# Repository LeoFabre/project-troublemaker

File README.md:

# 🚨PROJECT TROUBLEMAKER🚨 - ABANDONED, new project coming very soon
### The original dub soundsystem-style, fully digital, open source music preamp, based on ELK Audio OS.

This project is meant to be a fully digital sound system preamp, with a lot of features and a lot of fun to use. 
This would typically be used in a dub sound system control tower, right before the DSPs and power amps.
I am making it for [my own dub sound system](https://linktr.ee/mooncrownsoundsystem), but I am sharing it with the world so that everyone can enjoy and contribute to it.

### **_[Figma design of the front plate (click to open in figma) :](https://www.figma.com/design/a7w33TZh6XjIDETXx0zezs/PROJECT-TROUBLEMAKER?node-id=2-57&t=kPiumWiky9OcTQFE-1)_**

Please note that this project is still in its early stages, and it is not yet ready for use.
Also, the aim is not to provide a classic preamp to use with a microphone, but rather a preamp to use with a line-level signal, like a CD player, a computer, a synthesizer, etc.
It will NOT provide any protection for your speakers, and also will not split the signal into multiple bands outputs. 

It is meant to be used with a DSP that can handle multiple outputs, and optionally a mixer before it, to get microphone inputs and other line-level inputs.

**At the moment, the inputs and outputs are stereo only**, but more input modes will be added in the future (see Signal Flow section).

# [Software & Hardware stack (Click to open in whimsical)](https://whimsical.com/project-troublemaker-project-diagram-5eJmr8VAKfvCzGg2v3uwR2)

Project Troublemaker is based on [ELK Audio OS](https://elk-audio.github.io/elk-docs/html/index.html), which is a Linux-based realtime audio OS that can run VST3 plugins.  
It is **_HIGHLY RECOMMENDED_** to get a grasp of ELK Audio OS before diving into this project.

I use a [Raspberry pi 4 (8GB)](https://www.raspberrypi.com/products/raspberry-pi-4-model-b/) as the main board, 

a [HifiBerry DAC+ ADC Pro](https://www.hifiberry.com/shop/boards/hifiberry-dac-adc-pro/), to get audio I/O,

a [Teensy 4.1](https://www.pjrc.com/store/teensy41.html) as the control board, which acts as a MIDI controller and communicates with the Raspberry Pi via USB.

To build the control panel I use [CD74HC4067 multiplexers](https://www.amazon.fr/ICQUANZX-CD74HC4067-Analogique-Multiplexeur-Num%C3%A9rique/dp/B07VF14YNG), and a lot of [arcade buttons](https://www.smallcab.net/sanwa-obsc-24mm-translucent-pushbutton-purple-p-2462.html), [potentiometers](https://www.amazon.fr/dp/B07B64MWRF?ref=ppx_yo2ov_dt_b_fed_asin_title), [RGB LED sticks](https://fr.aliexpress.com/item/1005006344542138.html), and [switches](https://amazon.fr/dp/B09W4HBXJ7).

The project is meant to be a fully open source project, with all the source code and hardware design files available for free.

**_Because I strongly believe that music is meant to be shared, and music gear should be open source._**

Please feel free to contribute by opening a PR or an issue. 

**_Keep in mind that I am still learning, and that I am doing this project in my free time_**, so I may take some time to get back to you and updates may be slow.

# Featured Plugins (Work in Progress)
- **_[SampleTower](https://github.com/LeoFabre/SampleTower)_** : My JUCE-based VST3 sample player. features 11 fully-loaded-in-RAM sample slots, real-time playback speed control, sample loading from the file system (via config file), sample triggering with a MIDI note, one-shot and loop modes for each sample (via config file), kill button that stops all currently playing samples.
- 2 parametric EQs with bypass switches.
- **_[Moses](https://github.com/LeoFabre/Moses)_** : My fork of [IEM's multiband compressor](https://git.iem.at/audioplugins/IEMPluginSuite/-/tree/master/MultiBandCompressor?ref_type=heads). It is a 4-band SIMD optimized multiband compressor/crossover plugin, featuring cascaded Butterworth, linkwitz-riley filters and Allpass filters, solo&kill switches and master controls.
- **_[Strange Returns](https://github.com/LeoFabre/StrangeReturns-CMake)_** : My fork of JackWithOneEye's [Strange Returns](https://github.com/JackWithOneEye/StrangeReturns) delay plugin. 
- **_[Graindr](https://github.com/LeoFabre/Graindr)_** : My fork of JackWithOneEye's [Graindr](https://github.com/JackWithOneEye/Graindr), dual granular delay plugin.
- **_Parametric Reverb FX_** : A parametric reverb that I have yet to design. The reverb pots on the frontplate are inspired by ableton's reverb plugin, and are subject to change.
- **_Sub Roar FX_** : A classic dub sub bass roar effect based on saturation, and filtering, and reverb. It is only composed of BrickWorks plugins that ELK Audio OS provides, I may or may not make a JUCE version of it in the future.

# [Signal Flow (click to open in whimsical)](https://whimsical.com/project-troublemaker-signal-flow-PksJ2XxrEqBQ8Brrcc3UFW)

## Input modes
- **_Stereo mode_**: The default mode, where the HifiBerry is used as a stereo input and output.
- **_Aux send mode_** (to be implemented): The 2 stereo channels of the HifiBerry are split in 2 mono input channels and 2 mono output channels.   
The first mono input channel is used as the main input, the first mono output is used as the main output, the second mono input channel is used as the aux send, and the second mono input channel is used as the aux return.   
This is useful to send the signal to an external effect processor and get it back in the preamp, like a reverb or a delay, and then use the preamp's processing on it.

As of now, the modes are not implemented, and the preamp only works in stereo mode.  
In the future, I will add a switch to select the input mode at boot time (Sushi would then get its processor graph built by the glue app via gRPC instead of the config file).

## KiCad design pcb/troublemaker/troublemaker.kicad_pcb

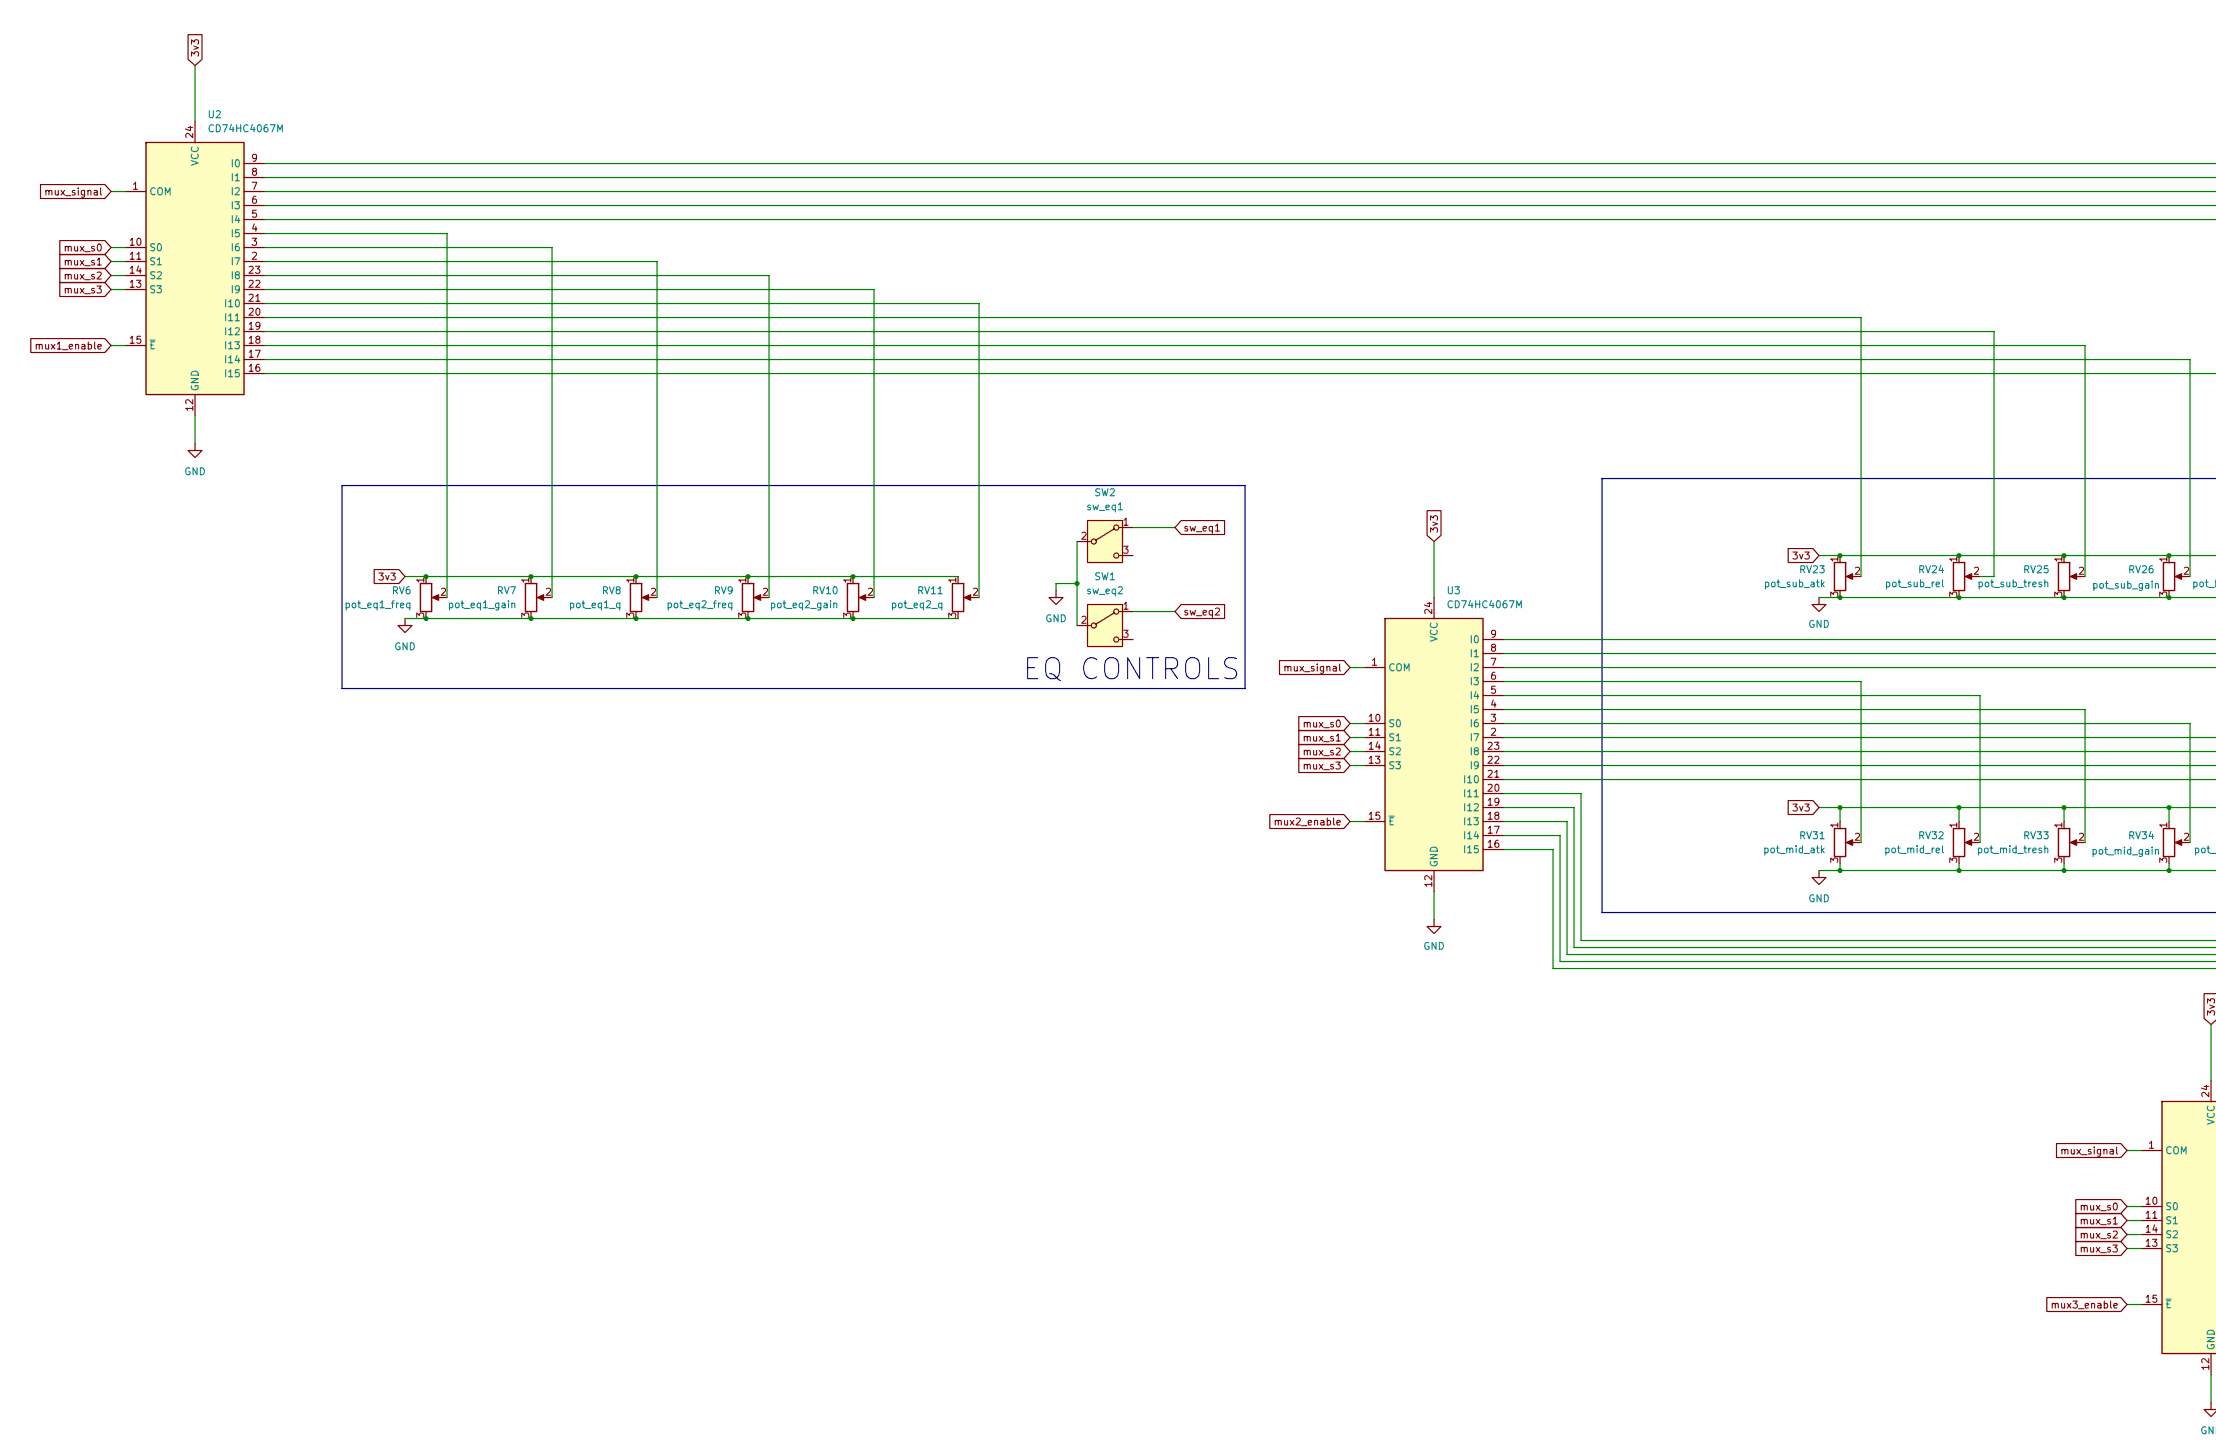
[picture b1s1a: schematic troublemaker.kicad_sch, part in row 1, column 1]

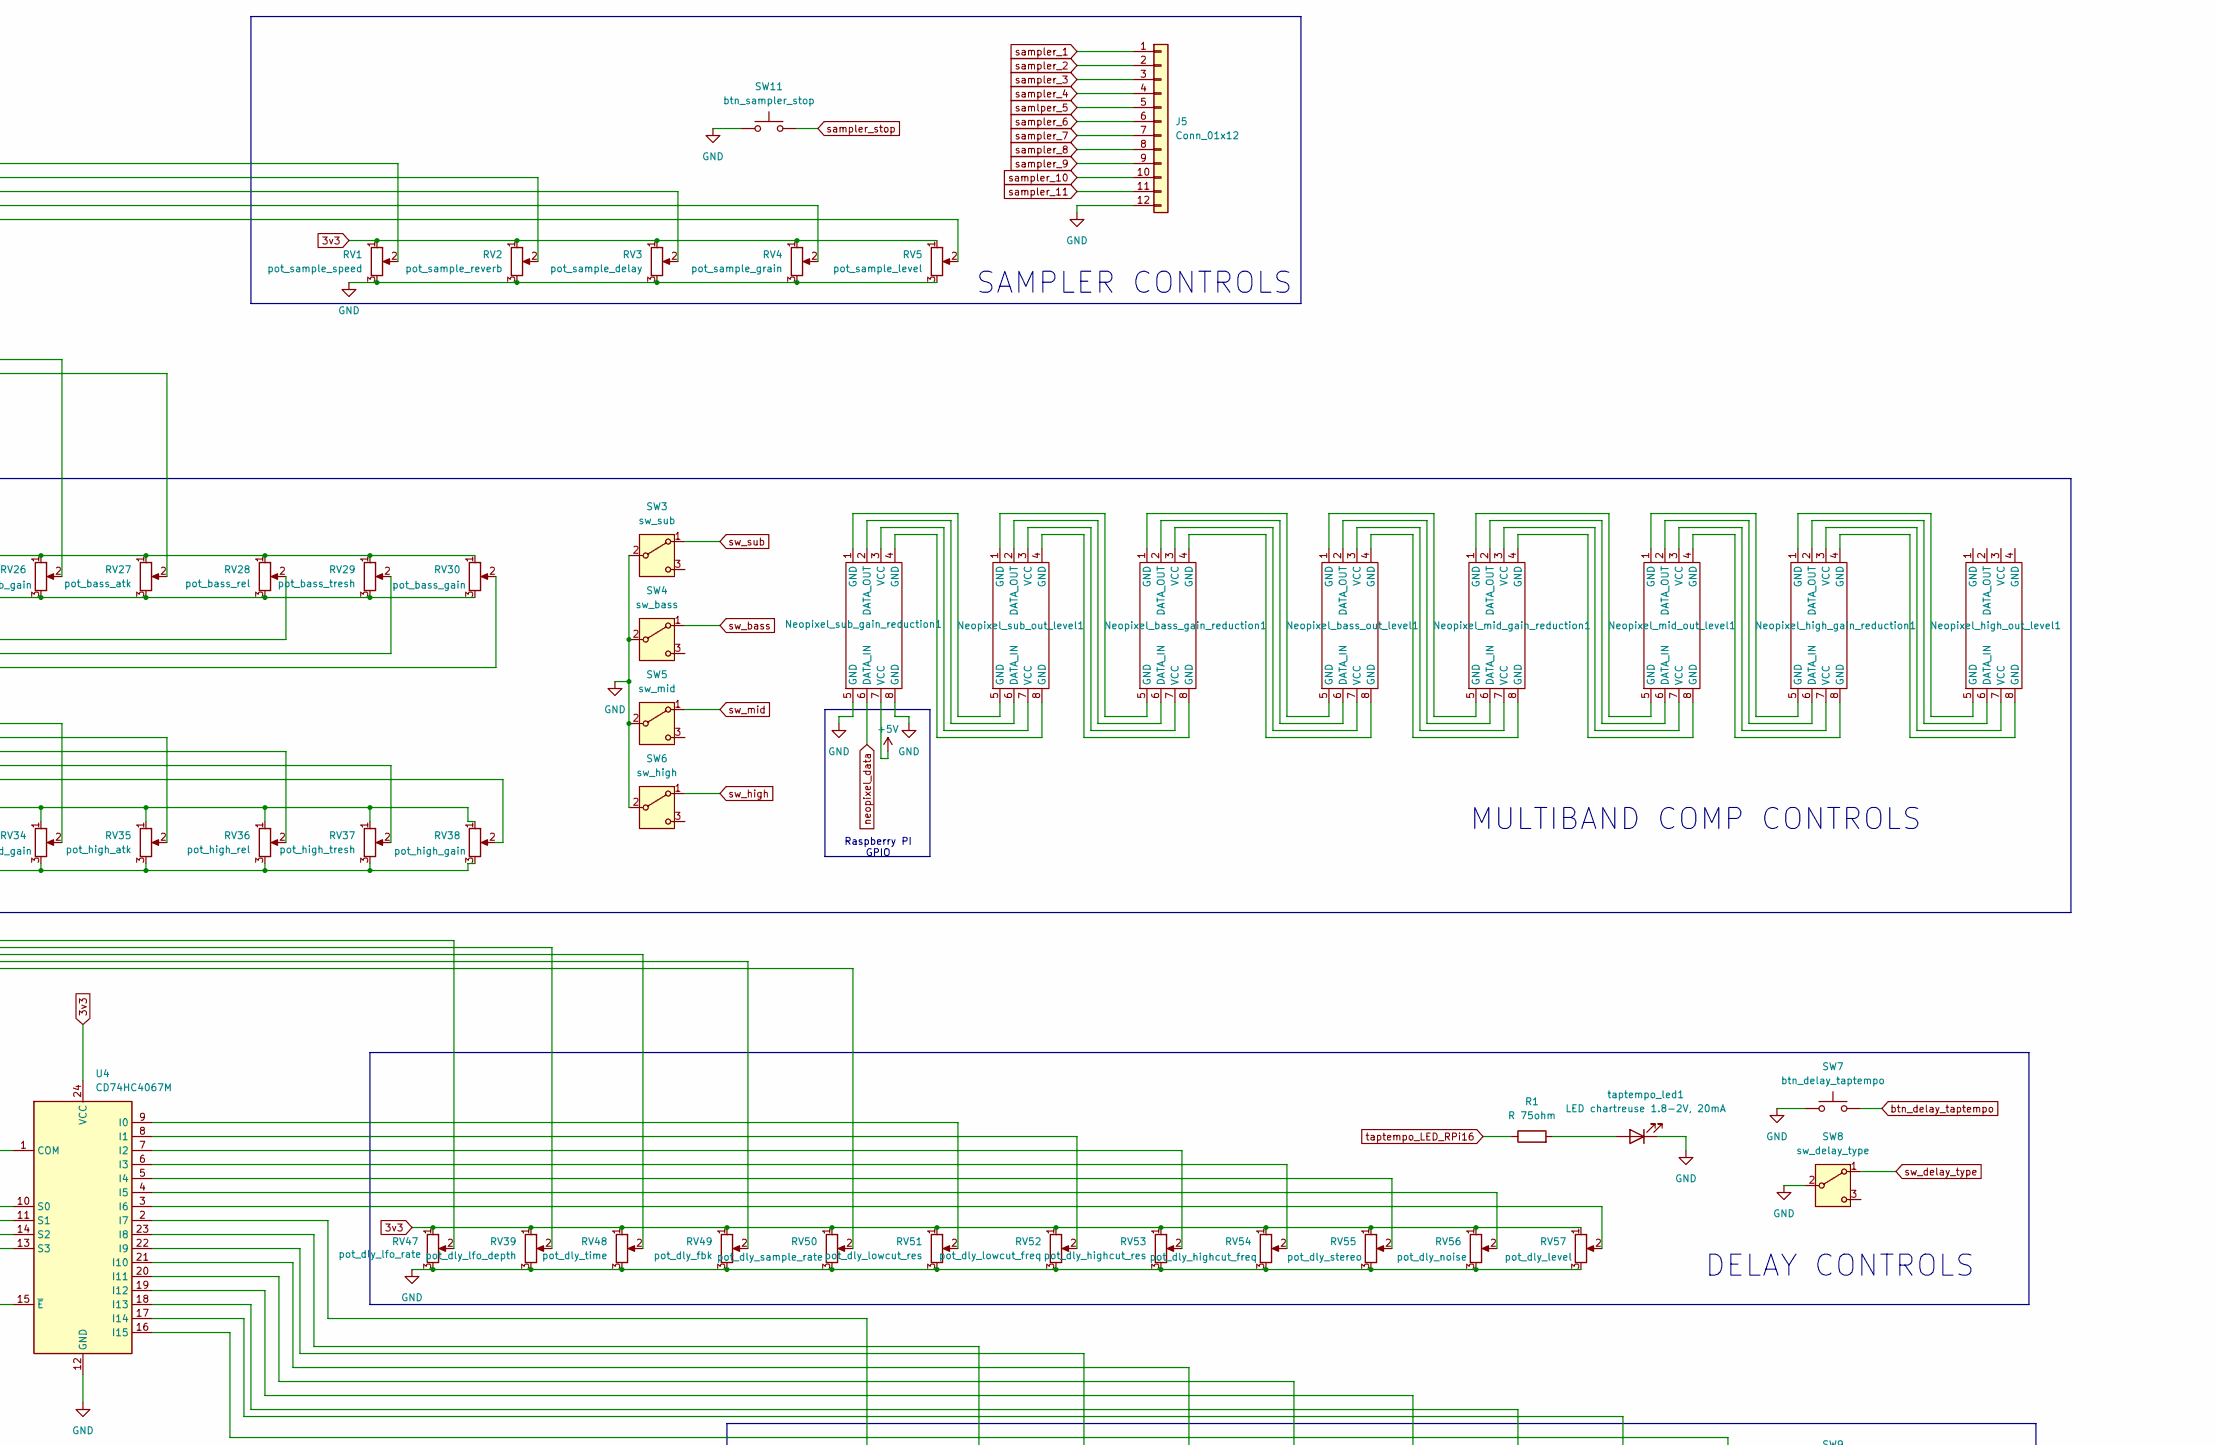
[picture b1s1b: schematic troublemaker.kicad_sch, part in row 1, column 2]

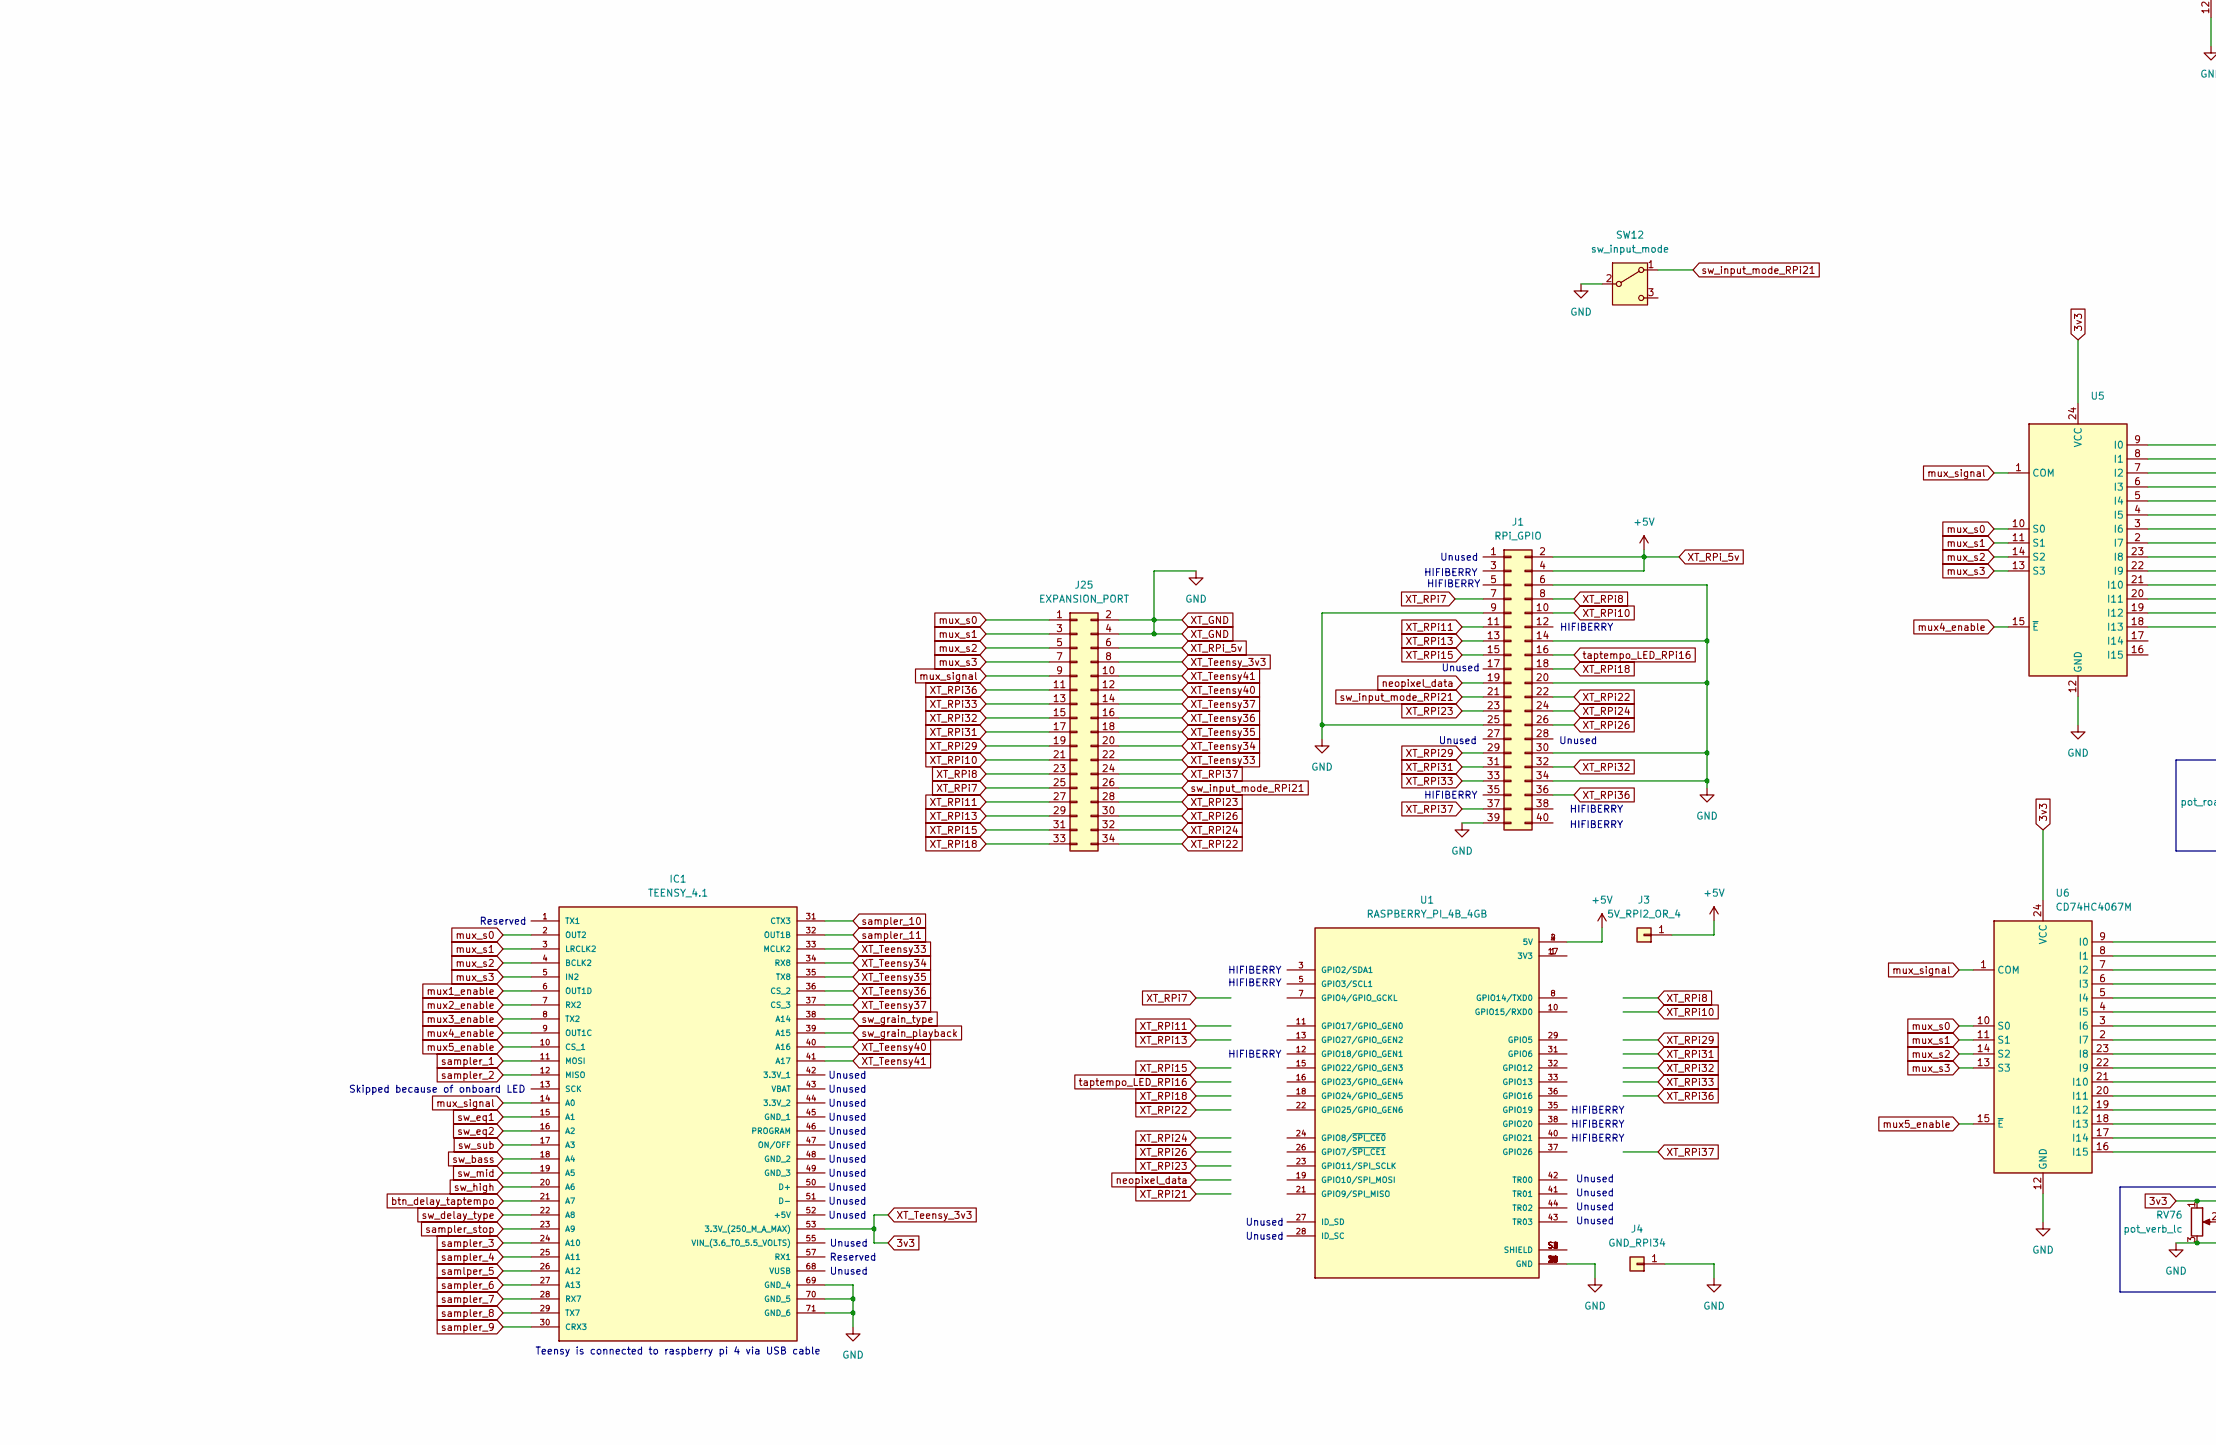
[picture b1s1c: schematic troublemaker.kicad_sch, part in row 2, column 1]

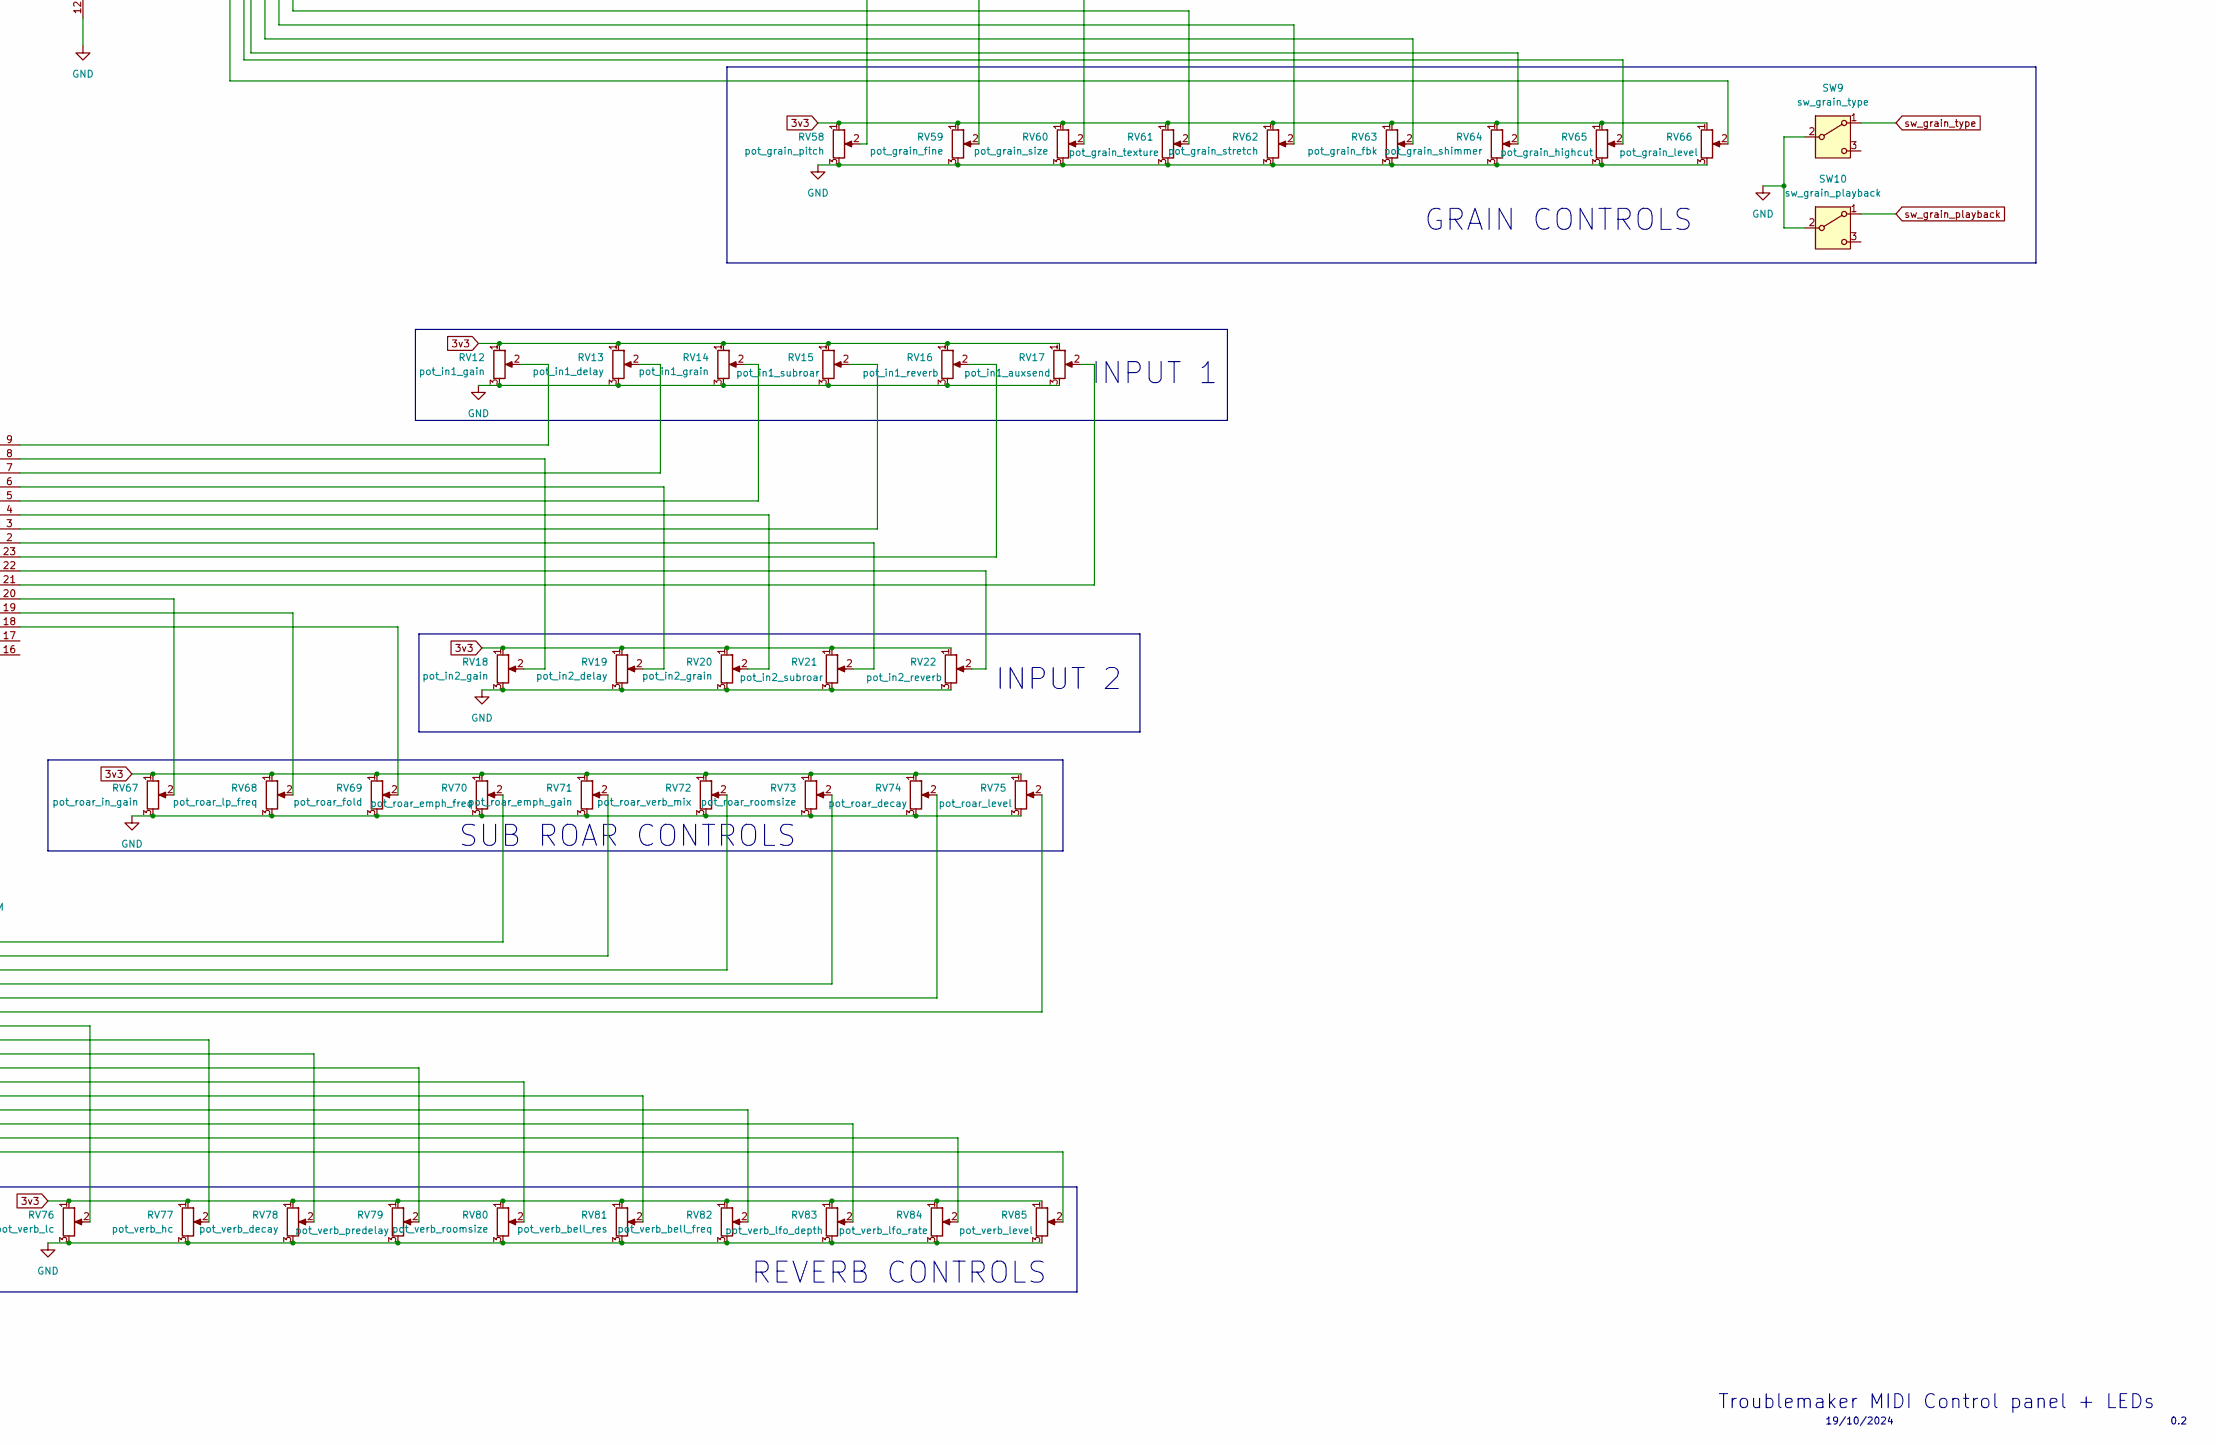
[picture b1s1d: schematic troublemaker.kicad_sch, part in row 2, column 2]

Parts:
IC1: TEENSY_4.1; TEENSY41; Manufacturer_Part_Number TEENSY 4.1
J1: RPi_GPIO; IDC-Header_2x20_P2.54mm_Vertical
J3: 5V_RPI2_OR_4; PinHeader_1x01_P1.00mm_Vertical
J4: GND_RPI34; PinHeader_1x01_P1.00mm_Vertical
J5: Conn_01x12; PinHeader_1x12_P2.00mm_Vertical
J25: EXPANSION_PORT; IDC-Header_2x17_P2.54mm_Vertical
Neopixel_bass_gain_reduction1: Neopixel-8LED
Neopixel_bass_out_level1: Neopixel-8LED
Neopixel_high_gain_reduction1: Neopixel-8LED
Neopixel_high_out_level1: Neopixel-8LED
Neopixel_mid_gain_reduction1: Neopixel-8LED
Neopixel_mid_out_level1: Neopixel-8LED
Neopixel_sub_gain_reduction1: Neopixel-8LED
Neopixel_sub_out_level1: Neopixel-8LED
R1: R 75ohm; R_Axial_DIN0207_L6.3mm_D2.5mm_P10.16mm_Horizontal
RV1: pot_sample_speed; Potentiometer_Alps_RK09K_Single_Vertical
RV2: pot_sample_reverb; Potentiometer_Alps_RK09K_Single_Vertical
RV3: pot_sample_delay; Potentiometer_Alps_RK09K_Single_Vertical
RV4: pot_sample_grain; Potentiometer_Alps_RK09K_Single_Vertical
RV5: pot_sample_level; Potentiometer_Alps_RK09K_Single_Vertical
RV6: pot_eq1_freq; Potentiometer_Alps_RK09K_Single_Vertical
RV7: pot_eq1_gain; Potentiometer_Alps_RK09K_Single_Vertical
RV8: pot_eq1_q; Potentiometer_Alps_RK09K_Single_Vertical
RV9: pot_eq2_freq; Potentiometer_Alps_RK09K_Single_Vertical
RV10: pot_eq2_gain; Potentiometer_Alps_RK09K_Single_Vertical
RV11: pot_eq2_q; Potentiometer_Alps_RK09K_Single_Vertical
RV12: pot_in1_gain; Potentiometer_Alps_RK09K_Single_Vertical
RV13: pot_in1_delay; Potentiometer_Alps_RK09K_Single_Vertical
RV14: pot_in1_grain; Potentiometer_Alps_RK09K_Single_Vertical
RV15: pot_in1_subroar; Potentiometer_Alps_RK09K_Single_Vertical
RV16: pot_in1_reverb; Potentiometer_Alps_RK09K_Single_Vertical
RV17: pot_in1_auxsend; Potentiometer_Alps_RK09K_Single_Vertical
RV18: pot_in2_gain; Potentiometer_Alps_RK09K_Single_Vertical
RV19: pot_in2_delay; Potentiometer_Alps_RK09K_Single_Vertical
RV20: pot_in2_grain; Potentiometer_Alps_RK09K_Single_Vertical
RV21: pot_in2_subroar; Potentiometer_Alps_RK09K_Single_Vertical
RV22: pot_in2_reverb; Potentiometer_Alps_RK09K_Single_Vertical
RV23: pot_sub_atk; Potentiometer_Alps_RK09K_Single_Vertical
RV24: pot_sub_rel; Potentiometer_Alps_RK09K_Single_Vertical
RV25: pot_sub_tresh; Potentiometer_Alps_RK09K_Single_Vertical
RV26: pot_sub_gain; Potentiometer_Alps_RK09K_Single_Vertical
RV27: pot_bass_atk; Potentiometer_Alps_RK09K_Single_Vertical
RV28: pot_bass_rel; Potentiometer_Alps_RK09K_Single_Vertical
RV29: pot_bass_tresh; Potentiometer_Alps_RK09K_Single_Vertical
RV30: pot_bass_gain; Potentiometer_Alps_RK09K_Single_Vertical
RV31: pot_mid_atk; Potentiometer_Alps_RK09K_Single_Vertical
RV32: pot_mid_rel; Potentiometer_Alps_RK09K_Single_Vertical
RV33: pot_mid_tresh; Potentiometer_Alps_RK09K_Single_Vertical
RV34: pot_mid_gain; Potentiometer_Alps_RK09K_Single_Vertical
RV35: pot_high_atk; Potentiometer_Alps_RK09K_Single_Vertical
RV36: pot_high_rel; Potentiometer_Alps_RK09K_Single_Vertical
RV37: pot_high_tresh; Potentiometer_Alps_RK09K_Single_Vertical
RV38: pot_high_gain; Potentiometer_Alps_RK09K_Single_Vertical
RV39: pot_dly_lfo_depth; Potentiometer_Alps_RK09K_Single_Vertical
RV47: pot_dly_lfo_rate; Potentiometer_Alps_RK09K_Single_Vertical
RV48: pot_dly_time; Potentiometer_Alps_RK09K_Single_Vertical
RV49: pot_dly_fbk; Potentiometer_Alps_RK09K_Single_Vertical
RV50: pot_dly_sample_rate; Potentiometer_Alps_RK09K_Single_Vertical
RV51: pot_dly_lowcut_res; Potentiometer_Alps_RK09K_Single_Vertical
RV52: pot_dly_lowcut_freq; Potentiometer_Alps_RK09K_Single_Vertical
RV53: pot_dly_highcut_res; Potentiometer_Alps_RK09K_Single_Vertical
RV54: pot_dly_highcut_freq; Potentiometer_Alps_RK09K_Single_Vertical
RV55: pot_dly_stereo; Potentiometer_Alps_RK09K_Single_Vertical
RV56: pot_dly_noise; Potentiometer_Alps_RK09K_Single_Vertical
RV57: pot_dly_level; Potentiometer_Alps_RK09K_Single_Vertical
RV58: pot_grain_pitch; Potentiometer_Alps_RK09K_Single_Vertical
RV59: pot_grain_fine; Potentiometer_Alps_RK09K_Single_Vertical
RV60: pot_grain_size; Potentiometer_Alps_RK09K_Single_Vertical
RV61: pot_grain_texture; Potentiometer_Alps_RK09K_Single_Vertical
RV62: pot_grain_stretch; Potentiometer_Alps_RK09K_Single_Vertical
RV63: pot_grain_fbk; Potentiometer_Alps_RK09K_Single_Vertical
RV64: pot_grain_shimmer; Potentiometer_Alps_RK09K_Single_Vertical
RV65: pot_grain_highcut; Potentiometer_Alps_RK09K_Single_Vertical
RV66: pot_grain_level; Potentiometer_Alps_RK09K_Single_Vertical
RV67: pot_roar_in_gain; Potentiometer_Alps_RK09K_Single_Vertical
RV68: pot_roar_lp_freq; Potentiometer_Alps_RK09K_Single_Vertical
RV69: pot_roar_fold; Potentiometer_Alps_RK09K_Single_Vertical
RV70: pot_roar_emph_freq; Potentiometer_Alps_RK09K_Single_Vertical
RV71: pot_roar_emph_gain; Potentiometer_Alps_RK09K_Single_Vertical
RV72: pot_roar_verb_mix; Potentiometer_Alps_RK09K_Single_Vertical
RV73: pot_roar_roomsize; Potentiometer_Alps_RK09K_Single_Vertical
RV74: pot_roar_decay; Potentiometer_Alps_RK09K_Single_Vertical
RV75: pot_roar_level; Potentiometer_Alps_RK09K_Single_Vertical
RV76: pot_verb_lc; Potentiometer_Alps_RK09K_Single_Vertical
RV77: pot_verb_hc; Potentiometer_Alps_RK09K_Single_Vertical
RV78: pot_verb_decay; Potentiometer_Alps_RK09K_Single_Vertical
RV79: pot_verb_predelay; Potentiometer_Alps_RK09K_Single_Vertical
RV80: pot_verb_roomsize; Potentiometer_Alps_RK09K_Single_Vertical
RV81: pot_verb_bell_res; Potentiometer_Alps_RK09K_Single_Vertical
RV82: pot_verb_bell_freq; Potentiometer_Alps_RK09K_Single_Vertical
RV83: pot_verb_lfo_depth; Potentiometer_Alps_RK09K_Single_Vertical
RV84: pot_verb_lfo_rate; Potentiometer_Alps_RK09K_Single_Vertical
RV85: pot_verb_level; Potentiometer_Alps_RK09K_Single_Vertical
SW1: sw_eq2; SW_SPDT_red_leozor
SW2: sw_eq1; SW_SPDT_red_leozor
SW3: sw_sub; SW_SPDT_red_leozor
SW4: sw_bass; SW_SPDT_red_leozor
SW5: sw_mid; SW_SPDT_red_leozor
SW6: sw_high; SW_SPDT_red_leozor
SW7: btn_delay_taptempo; arcade_service_button_leozor
SW8: sw_delay_type; SW_SPDT_red_leozor
SW9: sw_grain_type; SW_SPDT_red_leozor
SW10: sw_grain_playback; SW_SPDT_red_leozor
SW11: btn_sampler_stop; arcade_service_button_leozor
SW12: sw_input_mode; SW_SPDT_red_leozor
U1: RASPBERRY_PI_4B_4GB; MODULE_RASPBERRY_PI_4B_4GB; PARTREV 4
U2, U3, U4, U5, U6: CD74HC4067M; Breakout_HC4067_PTH_Only
taptempo_led1: LED chartreuse 1.8-2V, 20mA; LED_D3.0mm

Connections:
3v3: IC1.53 (3.3V_(250_M_A_MAX)), J25.8, RV1.1, RV2.1, RV3.1, RV4.1, RV5.1, RV6.1, RV7.1, RV8.1, RV9.1, RV10.1, RV11.1, RV12.1, RV13.1, RV14.1, RV15.1, RV16.1, RV17.1, RV18.1, RV19.1, RV20.1, RV21.1, RV22.1, RV23.1, RV24.1, RV25.1, RV26.1, RV27.1, RV28.1, RV29.1, RV30.1, RV31.1, RV32.1, RV33.1, RV34.1, RV35.1, RV36.1, RV37.1, RV38.1, RV39.1, RV47.1, RV48.1, RV49.1, RV50.1, RV51.1, RV52.1, RV53.1, RV54.1, RV55.1, RV56.1, RV57.1, RV58.1, RV59.1, RV60.1, RV61.1, RV62.1, RV63.1, RV64.1, RV65.1, RV66.1, RV67.1, RV68.1, RV69.1, RV70.1, RV71.1, RV72.1, RV73.1, RV74.1, RV75.1, RV76.1, RV77.1, RV78.1, RV79.1, RV80.1, RV81.1, RV82.1, RV83.1, RV84.1, RV85.1, U2.24 (VCC), U3.24 (VCC), U4.24 (VCC), U5.24 (VCC), U6.24 (VCC)
unnamed: Neopixel_bass_gain_reduction1.6 (DATA_IN), Neopixel_sub_out_level1.2 (DATA_OUT)
unnamed: Neopixel_bass_gain_reduction1.2 (DATA_OUT), Neopixel_bass_out_level1.6 (DATA_IN)
unnamed: Neopixel_bass_gain_reduction1.1 (GND), Neopixel_bass_out_level1.5 (GND)
unnamed: Neopixel_bass_gain_reduction1.4 (GND), Neopixel_bass_out_level1.8 (GND)
unnamed: Neopixel_bass_gain_reduction1.5 (GND), Neopixel_sub_out_level1.1 (GND)
unnamed: Neopixel_bass_gain_reduction1.8 (GND), Neopixel_sub_out_level1.4 (GND)
unnamed: Neopixel_bass_gain_reduction1.3 (VCC), Neopixel_bass_out_level1.7 (VCC)
unnamed: Neopixel_bass_gain_reduction1.7 (VCC), Neopixel_sub_out_level1.3 (VCC)
unnamed: Neopixel_bass_out_level1.2 (DATA_OUT), Neopixel_mid_gain_reduction1.6 (DATA_IN)
unnamed: Neopixel_bass_out_level1.1 (GND), Neopixel_mid_gain_reduction1.5 (GND)
unnamed: Neopixel_bass_out_level1.4 (GND), Neopixel_mid_gain_reduction1.8 (GND)
unnamed: Neopixel_bass_out_level1.3 (VCC), Neopixel_mid_gain_reduction1.7 (VCC)
unnamed: Neopixel_high_gain_reduction1.6 (DATA_IN), Neopixel_mid_out_level1.2 (DATA_OUT)
unnamed: Neopixel_high_gain_reduction1.2 (DATA_OUT), Neopixel_high_out_level1.6 (DATA_IN)
unnamed: Neopixel_high_gain_reduction1.1 (GND), Neopixel_high_out_level1.5 (GND)
unnamed: Neopixel_high_gain_reduction1.4 (GND), Neopixel_high_out_level1.8 (GND)
unnamed: Neopixel_high_gain_reduction1.5 (GND), Neopixel_mid_out_level1.1 (GND)
unnamed: Neopixel_high_gain_reduction1.8 (GND), Neopixel_mid_out_level1.4 (GND)
unnamed: Neopixel_high_gain_reduction1.3 (VCC), Neopixel_high_out_level1.7 (VCC)
unnamed: Neopixel_high_gain_reduction1.7 (VCC), Neopixel_mid_out_level1.3 (VCC)
unnamed: Neopixel_mid_gain_reduction1.2 (DATA_OUT), Neopixel_mid_out_level1.6 (DATA_IN)
unnamed: Neopixel_mid_gain_reduction1.1 (GND), Neopixel_mid_out_level1.5 (GND)
unnamed: Neopixel_mid_gain_reduction1.4 (GND), Neopixel_mid_out_level1.8 (GND)
unnamed: Neopixel_mid_gain_reduction1.3 (VCC), Neopixel_mid_out_level1.7 (VCC)
unnamed: Neopixel_sub_gain_reduction1.2 (DATA_OUT), Neopixel_sub_out_level1.6 (DATA_IN)
unnamed: Neopixel_sub_gain_reduction1.1 (GND), Neopixel_sub_out_level1.5 (GND)
unnamed: Neopixel_sub_gain_reduction1.4 (GND), Neopixel_sub_out_level1.8 (GND)
unnamed: Neopixel_sub_gain_reduction1.3 (VCC), Neopixel_sub_out_level1.7 (VCC)
unnamed: U1.1 (3V3), U1.17 (3V3)
unnamed: U1.S1 (SHIELD), U1.S2 (SHIELD), U1.S3 (SHIELD), U1.S4 (SHIELD)
unnamed: RV1.2, U2.9 (I0)
unnamed: RV2.2, U2.8 (I1)
unnamed: RV3.2, U2.7 (I2)
unnamed: RV4.2, U2.6 (I3)
unnamed: RV5.2, U2.5 (I4)
unnamed: RV6.2, U2.4 (I5)
unnamed: RV7.2, U2.3 (I6)
unnamed: RV8.2, U2.2 (I7)
unnamed: RV9.2, U2.23 (I8)
unnamed: RV10.2, U2.22 (I9)
unnamed: RV11.2, U2.21 (I10)
unnamed: RV23.2, U2.20 (I11)
unnamed: RV24.2, U2.19 (I12)
unnamed: RV25.2, U2.18 (I13)
unnamed: RV26.2, U2.17 (I14)
unnamed: RV27.2, U2.16 (I15)
unnamed: RV28.2, U3.9 (I0)
unnamed: RV29.2, U3.8 (I1)
unnamed: RV30.2, U3.7 (I2)
unnamed: RV31.2, U3.6 (I3)
unnamed: RV32.2, U3.5 (I4)
unnamed: RV33.2, U3.4 (I5)
unnamed: RV34.2, U3.3 (I6)
unnamed: RV35.2, U3.2 (I7)
unnamed: RV36.2, U3.23 (I8)
unnamed: RV37.2, U3.22 (I9)
unnamed: RV38.2, U3.21 (I10)
unnamed: RV47.2, U3.20 (I11)
unnamed: RV39.2, U3.19 (I12)
unnamed: RV48.2, U3.18 (I13)
unnamed: RV49.2, U3.17 (I14)
unnamed: RV50.2, U3.16 (I15)
unnamed: RV51.2, U4.9 (I0)
unnamed: RV52.2, U4.8 (I1)
unnamed: RV53.2, U4.7 (I2)
unnamed: RV54.2, U4.6 (I3)
unnamed: RV55.2, U4.5 (I4)
unnamed: RV56.2, U4.4 (I5)
unnamed: RV57.2, U4.3 (I6)
unnamed: RV58.2, U4.2 (I7)
unnamed: RV59.2, U4.23 (I8)
unnamed: RV60.2, U4.22 (I9)
unnamed: RV61.2, U4.21 (I10)
unnamed: RV62.2, U4.20 (I11)
unnamed: RV63.2, U4.19 (I12)
unnamed: RV64.2, U4.18 (I13)
unnamed: RV65.2, U4.17 (I14)
unnamed: RV66.2, U4.16 (I15)
unnamed: RV12.2, U5.9 (I0)
unnamed: RV18.2, U5.8 (I1)
unnamed: RV13.2, U5.7 (I2)
unnamed: RV19.2, U5.6 (I3)
unnamed: RV14.2, U5.5 (I4)
unnamed: RV20.2, U5.4 (I5)
unnamed: RV15.2, U5.3 (I6)
unnamed: RV21.2, U5.2 (I7)
unnamed: RV16.2, U5.23 (I8)
unnamed: RV22.2, U5.22 (I9)
unnamed: RV17.2, U5.21 (I10)
unnamed: RV67.2, U5.20 (I11)
unnamed: RV68.2, U5.19 (I12)
unnamed: RV69.2, U5.18 (I13)
unnamed: RV70.2, U6.9 (I0)
unnamed: RV71.2, U6.8 (I1)
unnamed: RV72.2, U6.7 (I2)
unnamed: RV73.2, U6.6 (I3)
unnamed: RV74.2, U6.5 (I4)
unnamed: RV75.2, U6.4 (I5)
unnamed: RV76.2, U6.3 (I6)
unnamed: RV77.2, U6.2 (I7)
unnamed: RV78.2, U6.23 (I8)
unnamed: RV79.2, U6.22 (I9)
unnamed: RV80.2, U6.21 (I10)
unnamed: RV81.2, U6.20 (I11)
unnamed: RV82.2, U6.19 (I12)
unnamed: RV83.2, U6.18 (I13)
unnamed: RV84.2, U6.17 (I14)
unnamed: RV85.2, U6.16 (I15)
unnamed: R1.2, taptempo_led1.2 (A)
XT_GND: IC1.69 (GND_4), IC1.70 (GND_5), IC1.71 (GND_6), J1.6, J1.9, J1.14, J1.20, J1.25, J1.30, J1.34, J1.39, J4.1, J5.12, J25.2, J25.4, Neopixel_sub_gain_reduction1.5 (GND), Neopixel_sub_gain_reduction1.8 (GND), RV1.3, RV2.3, RV3.3, RV4.3, RV5.3, RV6.3, RV7.3, RV8.3, RV9.3, RV10.3, RV11.3, RV12.3, RV13.3, RV14.3, RV15.3, RV16.3, RV17.3, RV18.3, RV19.3, RV20.3, RV21.3, RV22.3, RV23.3, RV24.3, RV25.3, RV26.3, RV27.3, RV28.3, RV29.3, RV30.3, RV31.3, RV32.3, RV33.3, RV34.3, RV35.3, RV36.3, RV37.3, RV38.3, RV39.3, RV47.3, RV48.3, RV49.3, RV50.3, RV51.3, RV52.3, RV53.3, RV54.3, RV55.3, RV56.3, RV57.3, RV58.3, RV59.3, RV60.3, RV61.3, RV62.3, RV63.3, RV64.3, RV65.3, RV66.3, RV67.3, RV68.3, RV69.3, RV70.3, RV71.3, RV72.3, RV73.3, RV74.3, RV75.3, RV76.3, RV77.3, RV78.3, RV79.3, RV80.3, RV81.3, RV82.3, RV83.3, RV84.3, RV85.3, SW1.2 (B), SW2.2 (B), SW3.2 (B), SW4.2 (B), SW5.2 (B), SW6.2 (B), SW7.1, SW8.2 (B), SW9.2 (B), SW10.2 (B), SW11.1, SW12.2 (B), U1.6 (GND), U1.9 (GND), U1.14 (GND), U1.20 (GND), U1.25 (GND), U1.30 (GND), U1.34 (GND), U1.39 (GND), U2.12 (GND), U3.12 (GND), U4.12 (GND), U5.12 (GND), U6.12 (GND), taptempo_led1.1 (K); also elsewhere on the board
XT_RPi7: J1.7, J25.25
XT_RPi8: J1.8, J25.23
XT_RPi10: J1.10, J25.21
XT_RPi11: J1.11, J25.27
XT_RPi13: J1.13, J25.29
XT_RPi15: J1.15, J25.31
XT_RPi18: J1.18, J25.33
XT_RPi22: J1.22, J25.34
XT_RPi23: J1.23, J25.28
XT_RPi24: J1.24, J25.32
XT_RPi26: J1.26, J25.30
XT_RPi29: J1.29, J25.19
XT_RPi31: J1.31, J25.17
XT_RPi32: J1.32, J25.15
XT_RPi33: J1.33, J25.13
XT_RPi36: J1.36, J25.11
XT_RPi37: J1.37, J25.24
XT_RPi_5v: J1.2, J1.4, J3.1, J25.6, Neopixel_sub_gain_reduction1.7 (VCC), U1.2 (5V), U1.4 (5V); also elsewhere on the board
XT_Teensy33: IC1.33 (MCLK2), J25.22
XT_Teensy34: IC1.34 (RX8), J25.20
XT_Teensy35: IC1.35 (TX8), J25.18
XT_Teensy36: IC1.36 (CS_2), J25.16
XT_Teensy37: IC1.37 (CS_3), J25.14
XT_Teensy40: IC1.40 (A16), J25.12
XT_Teensy41: IC1.41 (A17), J25.10
btn_delay_taptempo: IC1.21 (A7), SW7.2
mux1_enable: IC1.6 (OUT1D), U2.15 (~E)
mux2_enable: IC1.7 (RX2), U3.15 (~E)
mux3_enable: IC1.8 (TX2), U4.15 (~E)
mux4_enable: IC1.9 (OUT1C), U5.15 (~E)
mux5_enable: IC1.10 (CS_1), U6.15 (~E)
mux_s0: IC1.2 (OUT2), J25.1, U2.10 (S0), U3.10 (S0), U4.10 (S0), U5.10 (S0), U6.10 (S0)
mux_s1: IC1.3 (LRCLK2), J25.3, U2.11 (S1), U3.11 (S1), U4.11 (S1), U5.11 (S1), U6.11 (S1)
mux_s2: IC1.4 (BCLK2), J25.5, U2.14 (S2), U3.14 (S2), U4.14 (S2), U5.14 (S2), U6.14 (S2)
mux_s3: IC1.5 (IN2), J25.7, U2.13 (S3), U3.13 (S3), U4.13 (S3), U5.13 (S3), U6.13 (S3)
mux_signal: IC1.14 (A0), J25.9, U2.1 (COM), U3.1 (COM), U4.1 (COM), U5.1 (COM), U6.1 (COM)
neopixel_data: J1.19, Neopixel_sub_gain_reduction1.6 (DATA_IN)
samlper_5: IC1.26 (A12), J5.5
sampler_1: IC1.11 (MOSI), J5.1
sampler_2: IC1.12 (MISO), J5.2
sampler_3: IC1.24 (A10), J5.3
sampler_4: IC1.25 (A11), J5.4
sampler_6: IC1.27 (A13), J5.6
sampler_7: IC1.28 (RX7), J5.7
sampler_8: IC1.29 (TX7), J5.8
sampler_9: IC1.30 (CRX3), J5.9
sampler_10: IC1.31 (CTX3), J5.10
sampler_11: IC1.32 (OUT1B), J5.11
sampler_stop: IC1.23 (A9), SW11.2
sw_bass: IC1.18 (A4), SW4.1 (A)
sw_delay_type: IC1.22 (A8), SW8.1 (A)
sw_eq1: IC1.15 (A1), SW2.1 (A)
sw_eq2: IC1.16 (A2), SW1.1 (A)
sw_grain_playback: IC1.39 (A15), SW10.1 (A)
sw_grain_type: IC1.38 (A14), SW9.1 (A)
sw_high: IC1.20 (A6), SW6.1 (A)
sw_input_mode_RPi21: J1.21, J25.26, SW12.1 (A)
sw_mid: IC1.19 (A5), SW5.1 (A)
sw_sub: IC1.17 (A3), SW3.1 (A)
taptempo_LED_RPi16: J1.16, R1.1

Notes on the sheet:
HIFIBERRY
Skipped because of onboard LED
Unused
Unused
Troublemaker MIDI Control panel + LEDs
19/10/2024
Raspberry PI GPIO
SAMPLER CONTROLS
DELAY CONTROLS
EQ CONTROLS
Reserved
GRAIN CONTROLS
Teensy is connected to raspberry pi 4 via USB cable
INPUT 2
SUB ROAR CONTROLS
INPUT 1
REVERB CONTROLS
MULTIBAND COMP CONTROLS
0.2
